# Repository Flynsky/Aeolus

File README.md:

# AEOLUS
### STM32 based Drone Ecosystem
<table align="center">
  <tr>
    <td align="center"><b>ESC Board</b></td>
    <td align="center"><b>Flight Controller</b></td>
  </tr>
  <tr>
    <td align="center">
      
    </td>
    <td align="center">
      
    </td>
  </tr>
  <tr>
    <td colspan="2" align="center"><b>Ground Station Controller</b></td>
  </tr>
  <tr>
    <td colspan="2" align="center">
      
    </td>
  </tr>
</table>

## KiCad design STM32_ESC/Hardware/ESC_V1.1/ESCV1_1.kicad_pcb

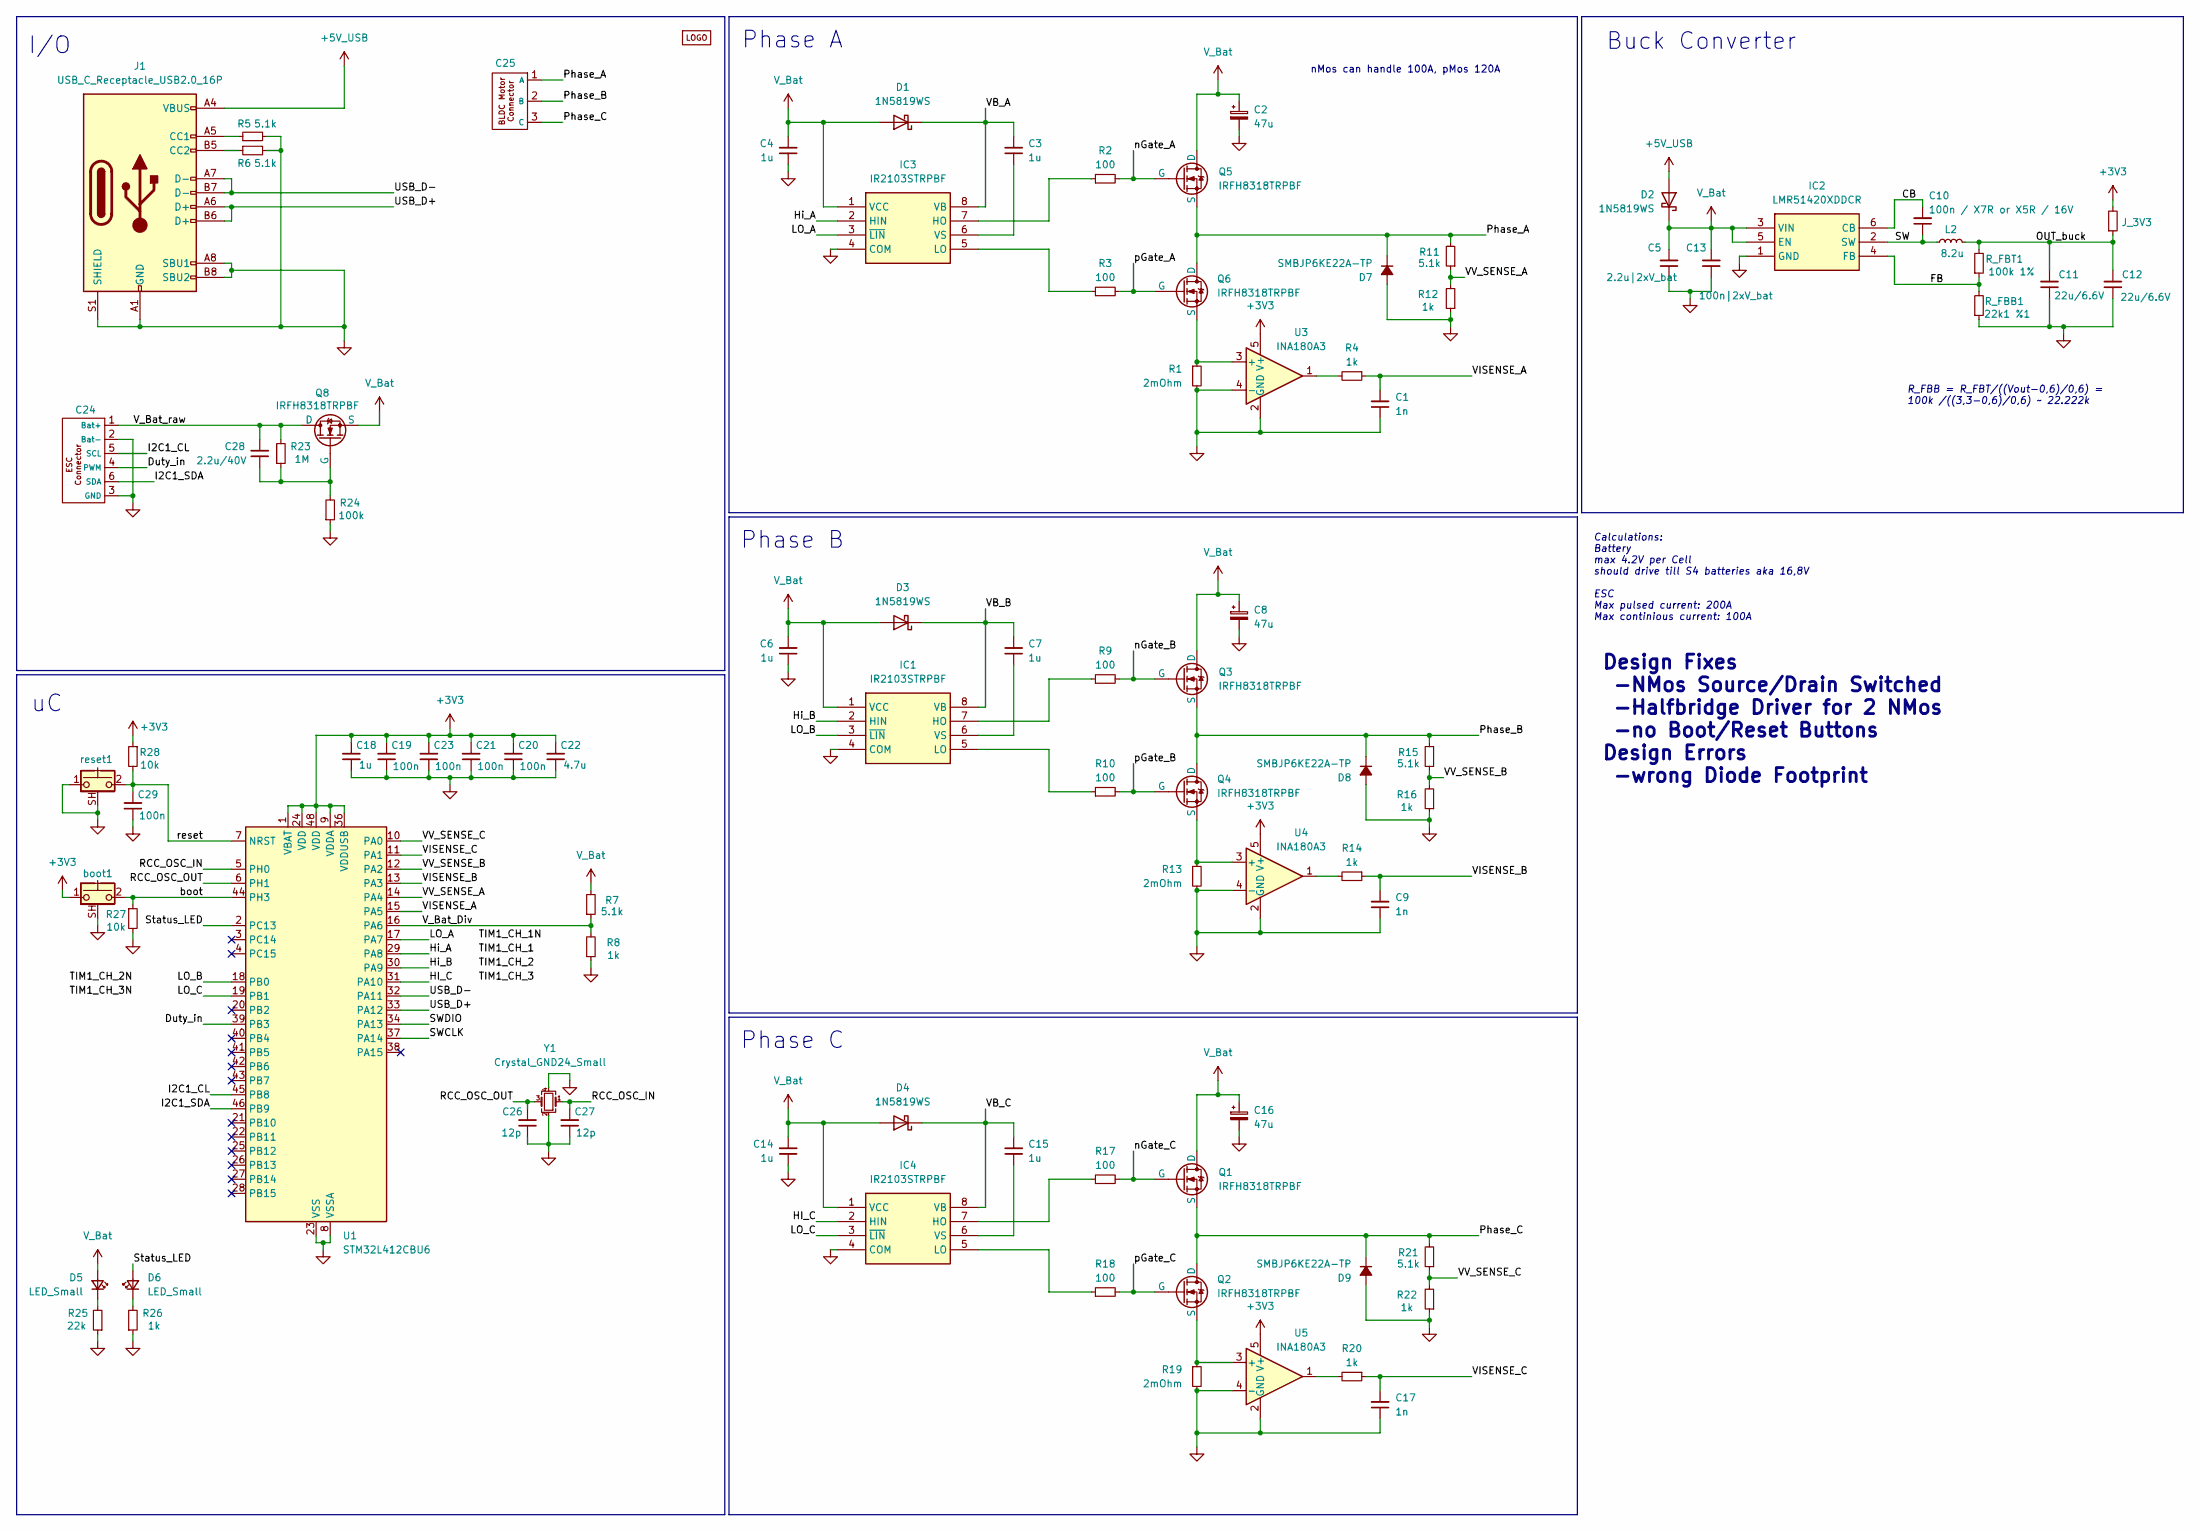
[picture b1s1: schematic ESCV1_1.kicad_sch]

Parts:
C1, C9, C17: 1n; C_0603_1608Metric
C2, C8, C16: 47u; Mouser Part Number 710-865080543009
C3, C4, C6, C7, C14, C15, C18: 1u; C_0603_1608Metric
C5: 2.2u|2xV_bat; C_0603_1608Metric
C10: 100n / X7R or X5R / 16V; C_0603_1608Metric
C11, C12: 22u/6.6V; C_0603_1608Metric
C13: 100n|2xV_bat; C_0402_1005Metric_Pad0.74x0.62mm_HandSolder
C19, C20, C21, C23, C29: 100n; C_0402_1005Metric
C22: 4.7u; C_0603_1608Metric
C24: Connector_ESC
C25: Connector_BLDC
C26, C27: 12p; C_0402_1005Metric
C28: 2.2u/40V; C_0603_1608Metric
D1, D2, D3, D4: 1N5819WS; D_SOD-323_HandSoldering
D5, D6: LED_Small; LED_0603_1608Metric
D7, D8, D9: SMBJP6KE22A-TP; D_SMB
IC1, IC3, IC4: IR2103STRPBF; Mouser Part Number 942-IR2103STRPBF
IC2: LMR51420XDDCR; Mouser Part Number 595-LMR51420XDDCR
J1: USB_C_Receptacle_USB2.0_16P; GSB1C41110SSHR
J_3V3: 0; R_0603_1608Metric
L2: 8.2u; Mouser Part Number 994-XAL5050-822MEC
Q1, Q2, Q3, Q4, Q5, Q6, Q8: IRFH8318TRPBF; BSC054N04NSGATMA1
R1, R13, R19: 2mOhm; R_2512_6332Metric; Mouser-Nr.: 603-PA2512FKM7W0R002
R2, R3, R9, R10, R17, R18: 100; R_0603_1608Metric
R4, R8, R12, R14, R16, R20, R22, R26: 1k; R_0603_1608Metric
R5, R6, R7, R11, R15, R21: 5.1k; R_0603_1608Metric
R23: 1M; R_0603_1608Metric
R24: 100k; R_0603_1608Metric
R25: 22k; R_0603_1608Metric
R27, R28: 10k; R_0603_1608Metric
R_FBB1: 22k1 %1; R_0603_1608Metric
R_FBT1: 100k 1%; R_0603_1608Metric
U1: STM32L412CBU6; QFN-48-1EP_7x7mm_P0.5mm_EP5.6x5.6mm
U3, U4, U5: INA180A3; SOT-23-5
U6: ESC_LOGO
Y1: Crystal_GND24_Small; ABM8W480000MHZ6D1XT3
boot1: CK_KMS2xxG; 435441019830
reset1: CK_KMS2xxG; 435441019830

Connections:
+3V3: C18.2, C19.2, C20.2, C21.2, C22.2, C23.2, J_3V3.2, R28.1, U1.1 (VBAT), U1.9 (VDDA), U1.24 (VDD), U1.36 (VDDUSB), U1.48 (VDD), U3.5 (V+), U4.5 (V+), U5.5 (V+), boot1.1
+5V_USB: D2.2 (A), J1.A4 (VBUS), J1.A9 (VBUS), J1.B4 (VBUS), J1.B9 (VBUS)
/CB: C10.2, IC2.6 (CB)
/Duty_in: C24.4 (PWM), U1.39 (PB3)
/FB: IC2.4 (FB), R_FBB1.2, R_FBT1.1
/HI_C: IC4.2 (HIN), U1.31 (PA10)
/Hi_A: IC3.2 (HIN), U1.29 (PA8)
/Hi_B: IC1.2 (HIN), U1.30 (PA9)
/I2C1_CL: C24.5 (SCL), U1.45 (PB8)
/I2C1_SDA: C24.6 (SDA), U1.46 (PB9)
/LO_A: IC3.3 (~LIN), U1.17 (PA7)
/LO_B: IC1.3 (~LIN), U1.18 (PB0)
/LO_C: IC4.3 (~LIN), U1.19 (PB1)
/OUT_buck: C11.2, C12.2, J_3V3.1, L2.2, R_FBT1.2
/Phase_A: C25.1 (A), D7.1 (K), Q5.S, Q6.D, R11.2
/Phase_B: C25.2 (B), D8.1 (K), Q3.S, Q4.D, R15.2
/Phase_C: C25.3 (C), D9.1 (K), Q1.S, Q2.D, R21.2
/RCC_OSC_IN: C27.2, U1.5 (PH0), Y1.1
/RCC_OSC_OUT: C26.2, U1.6 (PH1), Y1.3
/SW: C10.1, IC2.2 (SW), L2.1
/SWCLK: U1.37 (PA14)
/SWDIO: U1.34 (PA13)
/Status_LED: D6.2 (A), U1.2 (PC13)
/USB_D+: J1.A6 (D+), J1.B6 (D+), U1.33 (PA12)
/USB_D-: J1.A7 (D-), J1.B7 (D-), U1.32 (PA11)
/VB_A: C3.2, D1.1 (K), IC3.8 (VB)
/VB_B: C7.2, D3.1 (K), IC1.8 (VB)
/VB_C: C15.2, D4.1 (K), IC4.8 (VB)
/VISENSE_A: C1.2, R4.1, U1.15 (PA5)
/VISENSE_B: C9.2, R14.1, U1.13 (PA3)
/VISENSE_C: C17.2, R20.1, U1.11 (PA1)
/VV_SENSE_A: R11.1, R12.2, U1.14 (PA4)
/VV_SENSE_B: R15.1, R16.2, U1.12 (PA2)
/VV_SENSE_C: R21.1, R22.2, U1.10 (PA0)
/V_Bat_Div: R7.1, R8.2, U1.16 (PA6)
/V_Bat_raw: C24.1 (Bat+), C28.2, Q8.D, R23.2
/boot: R27.1, U1.44 (PH3), boot1.2
/nGate_A: Q5.G, R2.2
/nGate_B: Q3.G, R9.2
/nGate_C: Q1.G, R17.2
/pGate_A: Q6.G, R3.2
/pGate_B: Q4.G, R10.2
/pGate_C: Q2.G, R18.2
/reset: C29.2, R28.2, U1.7 (NRST), reset1.2
GND: C1.1, C2.2, C4.1, C5.1, C6.1, C8.2, C9.1, C11.1, C12.1, C13.1, C14.1, C16.2, C17.1, C18.1, C19.1, C20.1, C21.1, C22.1, C23.1, C24.2 (Bat-), C24.3 (GND), C26.1, C27.1, C29.1, D7.2 (A), D8.2 (A), D9.2 (A), IC1.4 (COM), IC2.1 (GND), IC3.4 (COM), IC4.4 (COM), J1.A1 (GND), J1.A8 (SBU1), J1.A12 (GND), J1.B1 (GND), J1.B8 (SBU2), J1.B12 (GND), J1.S1 (SHIELD), R1.2, R5.2, R6.2, R8.1, R12.1, R13.2, R16.1, R19.2, R22.1, R24.1, R25.1, R26.1, R27.2, R_FBB1.1, U1.8 (VSSA), U1.23 (VSS), U1.35 (VSS), U1.47 (VSS), U1.49 (VSS), U3.2 (GND), U3.4 (-), U4.2 (GND), U4.4 (-), U5.2 (GND), U5.4 (-), Y1.2, Y1.4, boot1.SH (B), reset1.1, reset1.SH (B)
unnamed: C28.1, Q8.G, R23.1, R24.2
unnamed: D5.1 (K), R25.2
unnamed: D6.1 (K), R26.2
unnamed: IC1.7 (HO), R9.1
unnamed: IC1.5 (LO), R10.1
unnamed: C7.1, IC1.6 (VS)
unnamed: IC3.7 (HO), R2.1
unnamed: IC3.5 (LO), R3.1
unnamed: C3.1, IC3.6 (VS)
unnamed: IC4.7 (HO), R17.1
unnamed: IC4.5 (LO), R18.1
unnamed: C15.1, IC4.6 (VS)
unnamed: J1.A5 (CC1), R5.1
unnamed: J1.B5 (CC2), R6.1
unnamed: R4.2, U3.1
unnamed: R14.2, U4.1
unnamed: R20.2, U5.1
unnamed: Q6.S, R1.1, U3.3 (+)
unnamed: Q4.S, R13.1, U4.3 (+)
unnamed: Q2.S, R19.1, U5.3 (+)
V_Bat: C2.1, C4.2, C5.2, C6.2, C8.1, C13.2, C14.2, C16.1, D1.2 (A), D2.1 (K), D3.2 (A), D4.2 (A), D5.2 (A), IC1.1 (VCC), IC2.3 (VIN), IC2.5 (EN), IC3.1 (VCC), IC4.1 (VCC), Q1.D, Q3.D, Q5.D, Q8.S, R7.2

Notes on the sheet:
Phase A
nMos can handle 100A, pMos 120A
Design Fixes -NMos Source/Drain Switched -Halfbridge Driver for 2 NMos -no Boot/Reset Buttons Design Errors -wrong Diode Footprint
I/O
Buck Converter
Phase B
Phase C
Calculations: Battery max 4.2V per Cell should drive till S4 batteries aka 16,8V ESC Max pulsed current: 200A Max continious current: 100A
R_FBB = R_FBT/((Vout-0,6)/0,6) = 100k /((3,3-0,6)/0,6) ~ 22.222k

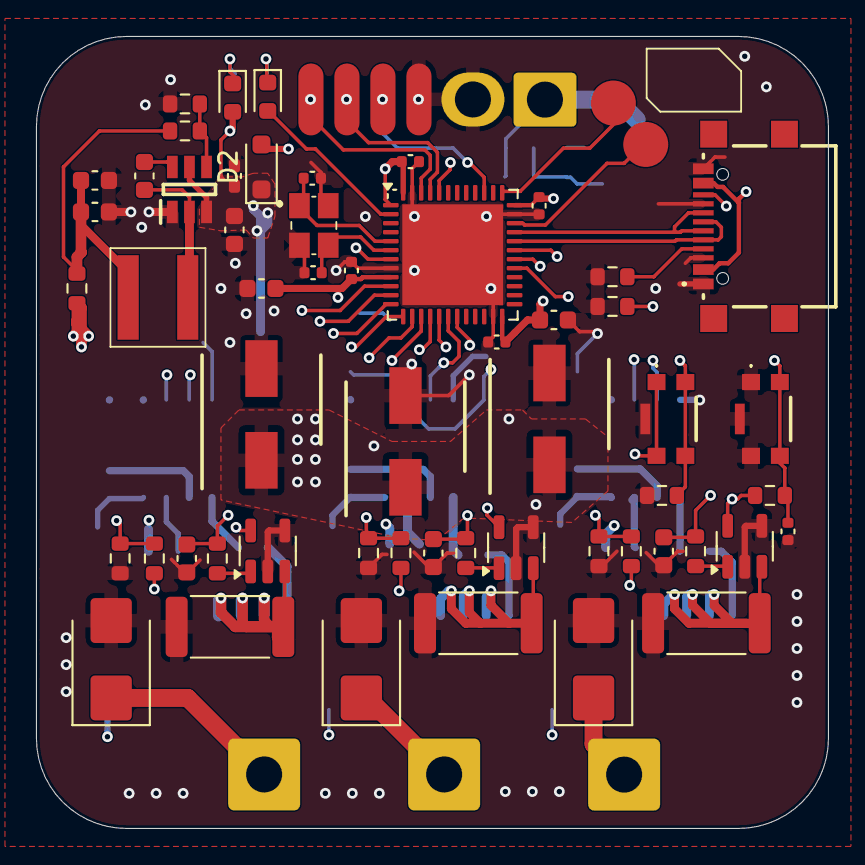
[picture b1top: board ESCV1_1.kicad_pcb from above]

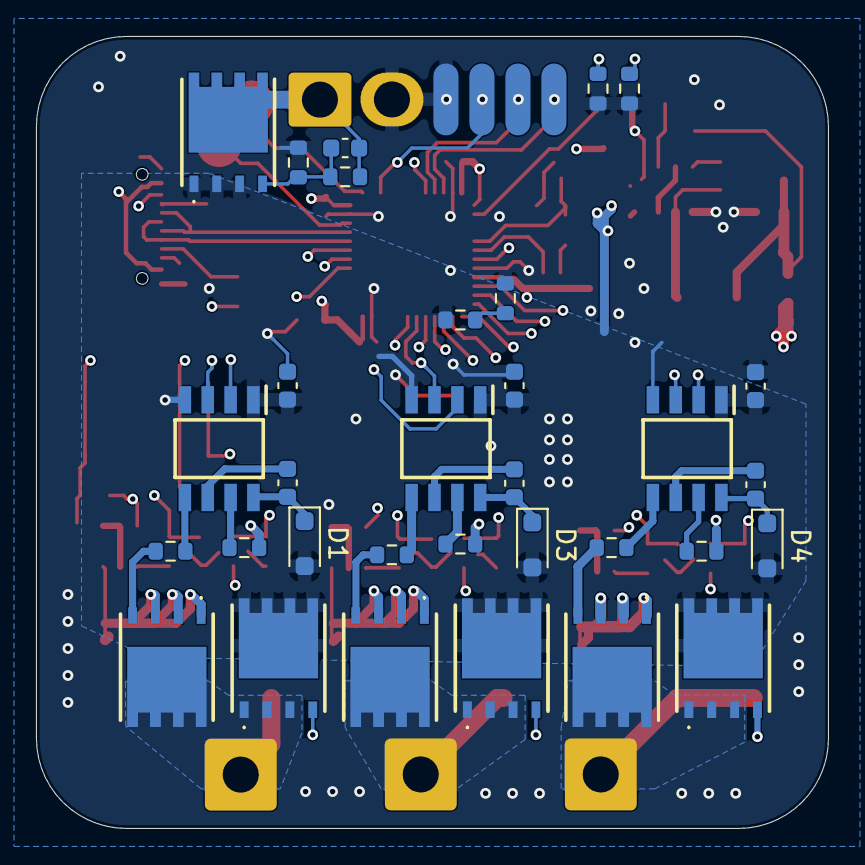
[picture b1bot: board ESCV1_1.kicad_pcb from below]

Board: 4 copper layers, 44.0 x 44.0 mm, 90 parts (32 on the bottom side), 64 nets.

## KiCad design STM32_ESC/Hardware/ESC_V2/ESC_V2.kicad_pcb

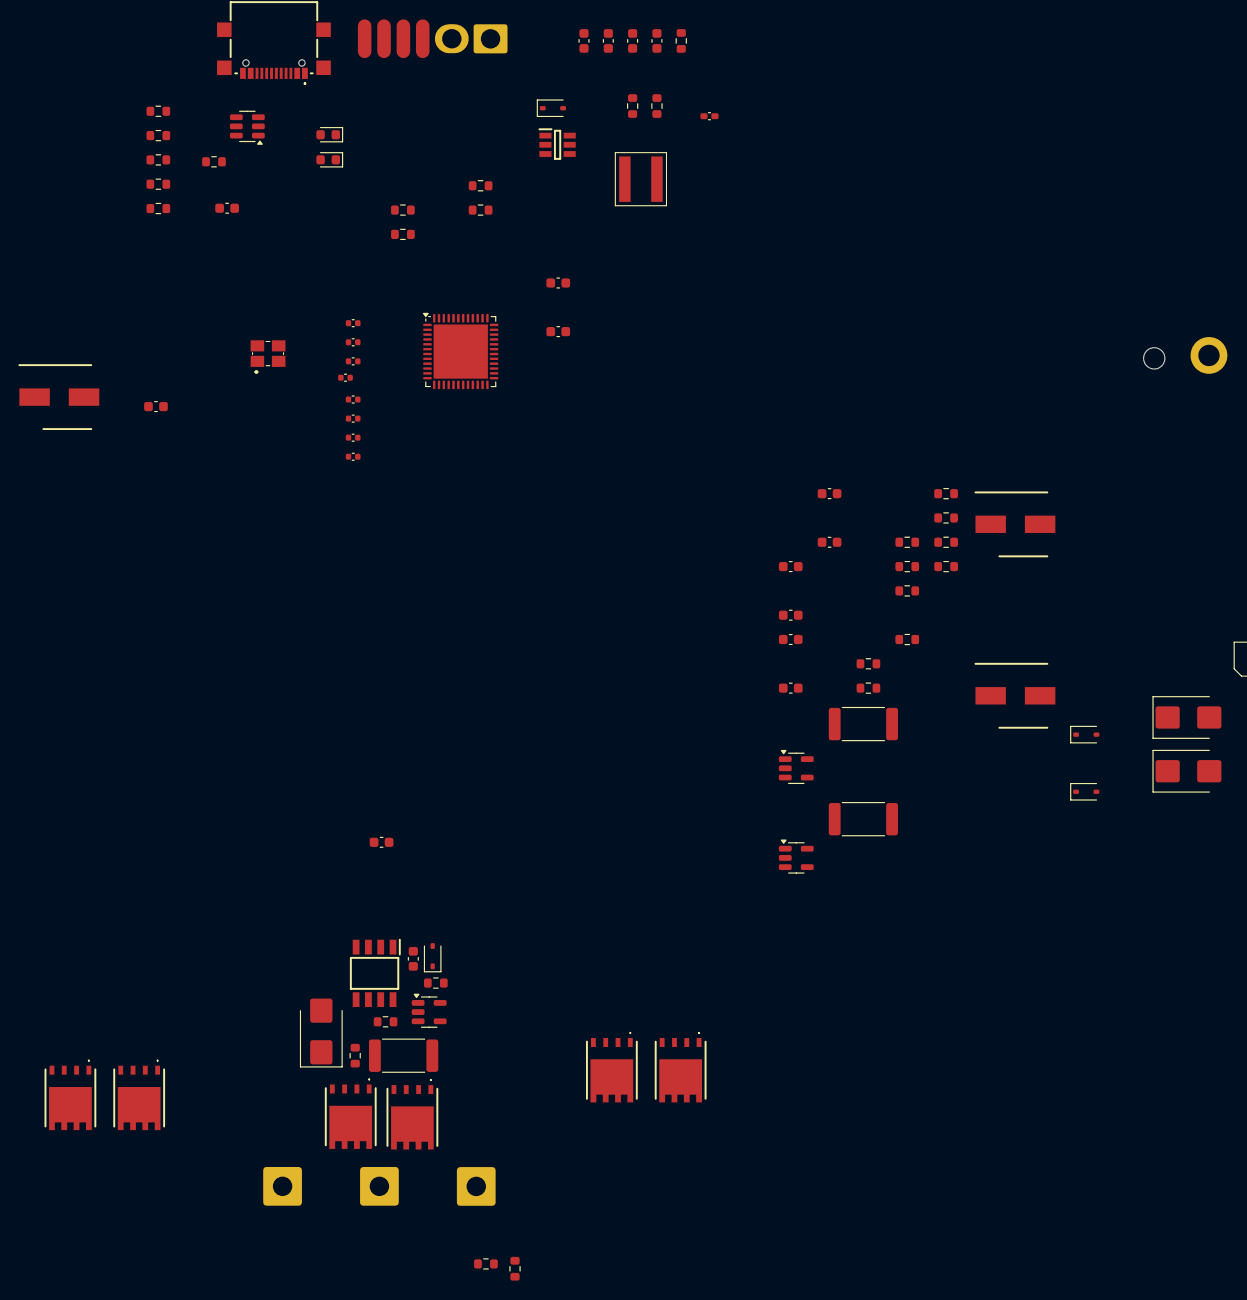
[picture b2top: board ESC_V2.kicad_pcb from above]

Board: 2 copper layers, 89 parts (0 on the bottom side), 55 nets, no tracks yet.

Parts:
C1: Connector_ESC
C2: 4.7u; C_0603_1608Metric
C3, C4, C6, C7, C29, C30: 100n; C_0402_1005Metric
C5: 2.2u/40V; C_0603_1608Metric
C8, C12, C13, C14, C15, C16, C17: 1u; C_0603_1608Metric
C9: Connector_BLDC
C10, C11: 12p; C_0402_1005Metric
C18, C19, C20: 47u; CAPAE660X550N
C21, C22, C23: 1n; C_0603_1608Metric
C24: 2.2u / 2xV_bat; C_0603_1608Metric
C25: 100n /2x V_bat; C_0402_1005Metric_Pad0.74x0.62mm_HandSolder
C26: 100n / X7R or X5R / 16V; C_0603_1608Metric
C27, C28: 22u/6.6V; C_0603_1608Metric
D1, D2: LED_Small; LED_0603_1608Metric
D3, D4, D5, D9: 1N5819WS; D_SOD-323
D6, D7, D8: SMBJP6KE22A-TP; D_SMB
H1: MountingHole; MountingHole_2.2mm_M2_DIN965_Pad
H2: MountingHole; MountingHole_2.2mm_M2
IC2: IR2103STRPBF; SOIC127P600X175-8N
IC4: LMR51420XDDCR; SOT95P280X110-6N
J1: USB_C_Receptacle_USB2.0_16P; GSB1C41110SSHR
J_3V1: 0; R_0603_1608Metric
L1: 8.2u; XAL5050822MEC
Q1, Q2, Q3, Q4, Q5, Q6: N-MOS IRFH8318TRPBF; BSC054N04NSGATMA1
R1, R2, R7, R21, R23, R25: 5.1k; R_0603_1608Metric
R3: 1M; R_0603_1608Metric
R4, R27, R28: 100k; R_0603_1608Metric
R5: 22k; R_0603_1608Metric
R6, R8, R18, R19, R20, R22, R24, R26: 1k; R_0603_1608Metric
R9, R10, R11, R12, R13, R14: 100; R_0603_1608Metric
R15, R16, R17: 2mOhm; R_2512_6332Metric
R_FBB1: 22k1 %1; R_0603_1608Metric
R_FBT1: 100k 1%; R_0603_1608Metric
U1: STM32L412CBU6; QFN-48-1EP_7x7mm_P0.5mm_EP5.6x5.6mm
U2: USBLC6-2SC6; SOT-23-6
U3: ESC_LOGO
U4, U5, U6: INA180A3; SOT-23-5
Y1: Crystal_GND24_Small; ABM8W480000MHZ6D1XT3

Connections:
+3V3: C2.2, C3.2, C4.2, C6.2, C7.2, C8.2, D2.2 (A), J_3V1.2, U1.1 (VBAT), U1.9 (VDDA), U1.24 (VDD), U1.36 (VDDUSB), U1.48 (VDD), U4.5 (V+), U5.5 (V+), U6.5 (V+)
+5V_USB: D9.2 (A), J1.A4 (VBUS), J1.A9 (VBUS), U2.5 (VBUS)
/CB: C26.2, IC4.6 (CB)
/Duty_in: C1.4 (PWM), U1.39 (PB3)
/FB: IC4.4 (FB), R_FBB1.2, R_FBT1.1
/Hi_B: IC2.2 (HIN), U1.30 (PA9)
/I2C1_CL: C1.5 (SCL), U1.45 (PB8)
/I2C1_SDA: C1.6 (SDA), U1.46 (PB9)
/LO_B: IC2.3 (~LIN), U1.18 (PB0)
/OUT_buck: C27.2, C28.2, J_3V1.1, L1.2, R_FBT1.2
/Phase_A: C9.1 (A), D8.1 (K), Q1.3 (D), Q2.1 (S), R25.2
/Phase_B: C9.2 (B), D6.1 (K), Q3.1 (S), Q4.3 (D), R21.2
/Phase_C: C9.3 (C), D7.1 (K), Q5.1 (S), Q6.3 (D), R23.2
/RCC_OSC_IN: C11.2, U1.5 (PH0), Y1.1
/RCC_OSC_OUT: C10.2, U1.6 (PH1), Y1.3
/SW: C26.1, IC4.2 (SW), L1.1
/USB_D+: U1.33 (PA12), U2.4 (I/O2)
/USB_D-: U1.32 (PA11), U2.6 (I/O1)
/VB_A: C15.2, D3.1 (K)
/VB_B: C16.2, D4.1 (K), IC2.8 (VB)
/VB_C: C17.2, D5.1 (K)
/VISENSE_A: C21.2, R18.1, U1.15 (PA5)
/VISENSE_B: C22.2, R19.1, U1.13 (PA3)
/VISENSE_C: C23.2, R20.1, U1.11 (PA1)
/VV_SENSE_A: R25.1, R26.2, U1.14 (PA4)
/VV_SENSE_B: R21.1, R22.2, U1.12 (PA2)
/VV_SENSE_C: R23.1, R24.2, U1.10 (PA0)
/V_Bat_Div: R7.1, R8.2, U1.16 (PA6)
/V_Bat_raw: C1.1 (Bat+), C5.2, R3.2
/nGate_A: Q2.2 (G), R9.2
/nGate_B: Q3.2 (G), R11.2
/nGate_C: Q5.2 (G), R13.2
/pGate_A: Q1.2 (G), R10.2
/pGate_B: Q4.2 (G), R12.2
/pGate_C: Q6.2 (G), R14.2
GND: C1.2 (Bat-), C1.3 (GND), C2.1, C3.1, C4.1, C6.1, C7.1, C8.1, C10.1, C11.1, C12.1, C13.1, C14.1, C18.2, C19.2, C20.2, C21.1, C22.1, C23.1, C24.1, C25.1, C27.1, C28.1, C29.1, C30.1, D6.2 (A), D7.2 (A), D8.2 (A), IC2.4 (COM), IC4.1 (GND), J1.A1 (GND), J1.A8 (SBU1), J1.A12 (GND), J1.B8 (SBU2), R1.2, R2.2, R4.1, R5.1, R6.1, R8.1, R15.2, R16.2, R17.2, R22.1, R24.1, R26.1, R27.1, R28.1, R_FBB1.1, U1.8 (VSSA), U1.23 (VSS), U1.35 (VSS), U1.47 (VSS), U1.49 (VSS), U2.2 (GND), U4.2 (GND), U4.4 (-), U5.2 (GND), U5.4 (-), U6.2 (GND), U6.4 (-), Y1.2, Y1.4
unnamed: C5.1, R3.1, R4.2
unnamed: D1.1 (K), R5.2
unnamed: D2.1 (K), R6.2
unnamed: IC2.7 (HO), R11.1
unnamed: IC2.5 (LO), R12.1
unnamed: C16.1, IC2.6 (VS)
unnamed: J1.A5 (CC1), R1.1
unnamed: J1.B5 (CC2), R2.1
unnamed: J1.A6 (D+), J1.B6 (D+), U2.3 (I/O2)
unnamed: J1.A7 (D-), J1.B7 (D-), U2.1 (I/O1)
unnamed: Q1.1 (S), R15.1, U4.3 (+)
unnamed: Q4.1 (S), R16.1, U5.3 (+)
unnamed: Q6.1 (S), R17.1, U6.3 (+)
unnamed: R18.2, U4.1
unnamed: R19.2, U5.1
unnamed: R20.2, U6.1
unnamed: C29.2, R27.2, U1.44 (PH3)
unnamed: C30.2, R28.2, U1.7 (NRST)
V_Bat: C12.2, C13.2, C14.2, C18.1, C19.1, C20.1, C24.2, C25.2, D1.2 (A), D3.2 (A), D4.2 (A), D5.2 (A), D9.1 (K), IC2.1 (VCC), IC4.3 (VIN), IC4.5 (EN), Q2.3 (D), Q3.3 (D), Q5.3 (D), R7.2

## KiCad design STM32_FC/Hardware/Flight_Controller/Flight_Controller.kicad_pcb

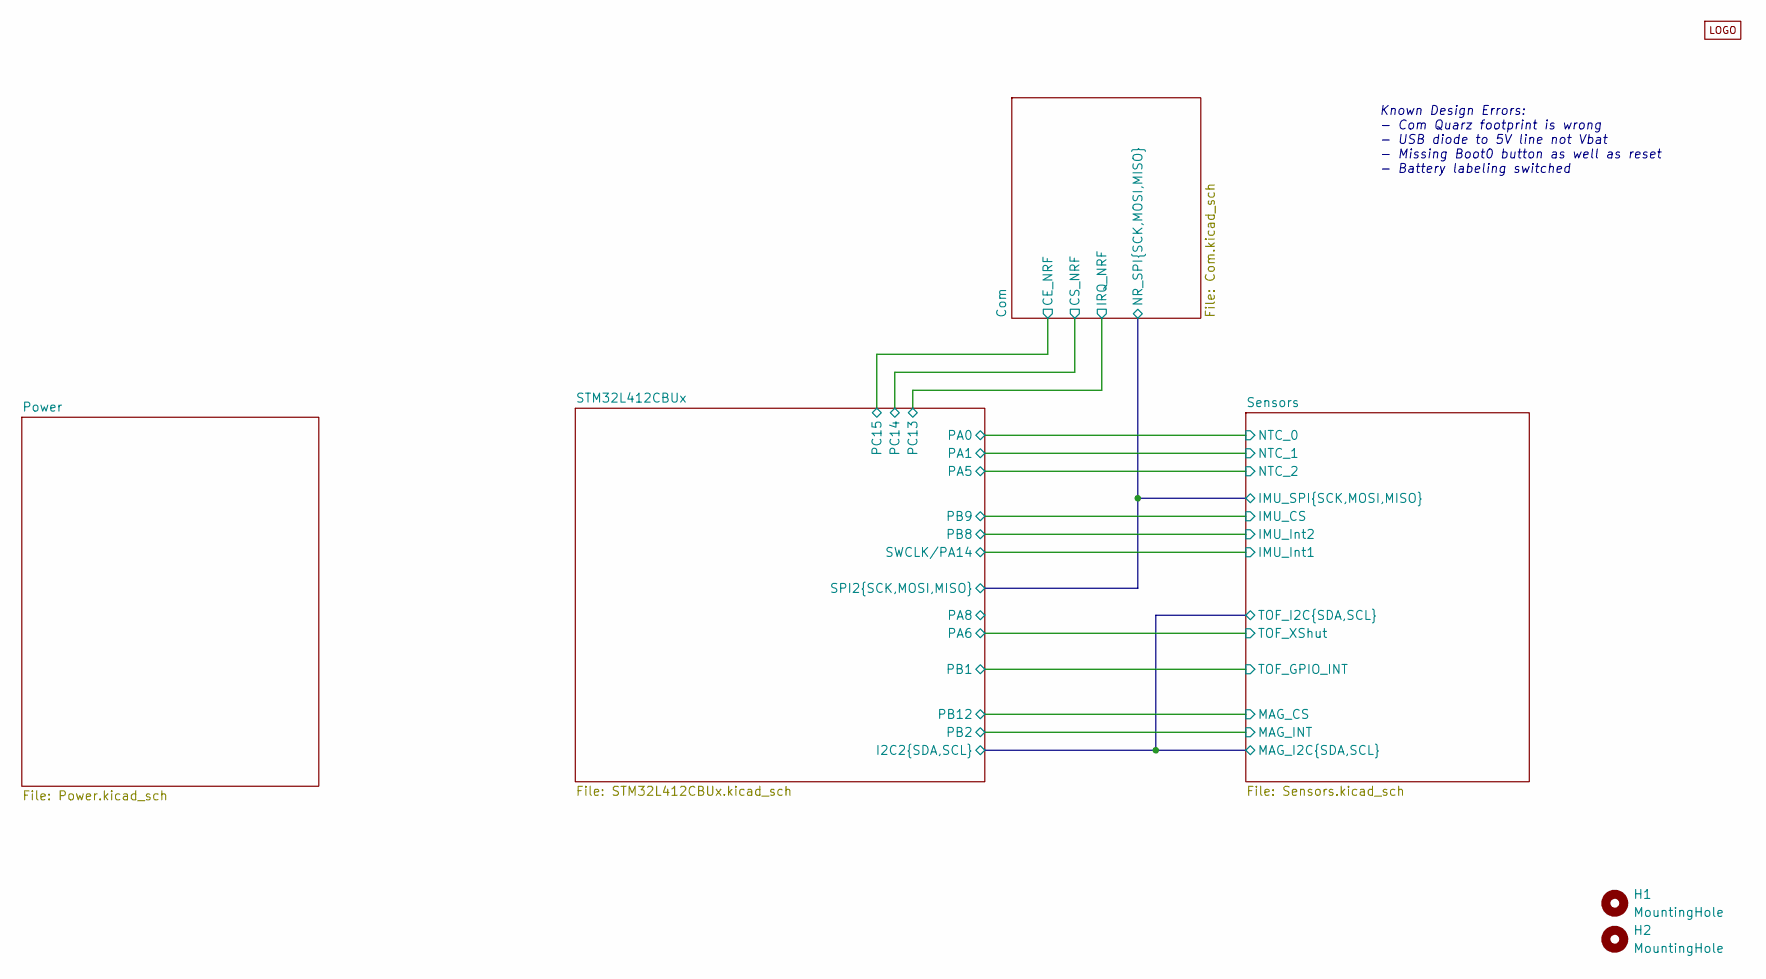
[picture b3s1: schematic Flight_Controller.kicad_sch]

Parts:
H1: MountingHole; MountingHole_2.2mm_M2_DIN965_Pad
H2: MountingHole; MountingHole_2.2mm_M2
U6: ESC_LOGO

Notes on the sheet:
Known Design Errors: - Com Quarz footprint is wrong - USB diode to 5V line not Vbat - Missing Boot0 button as well as reset - Battery labeling switched

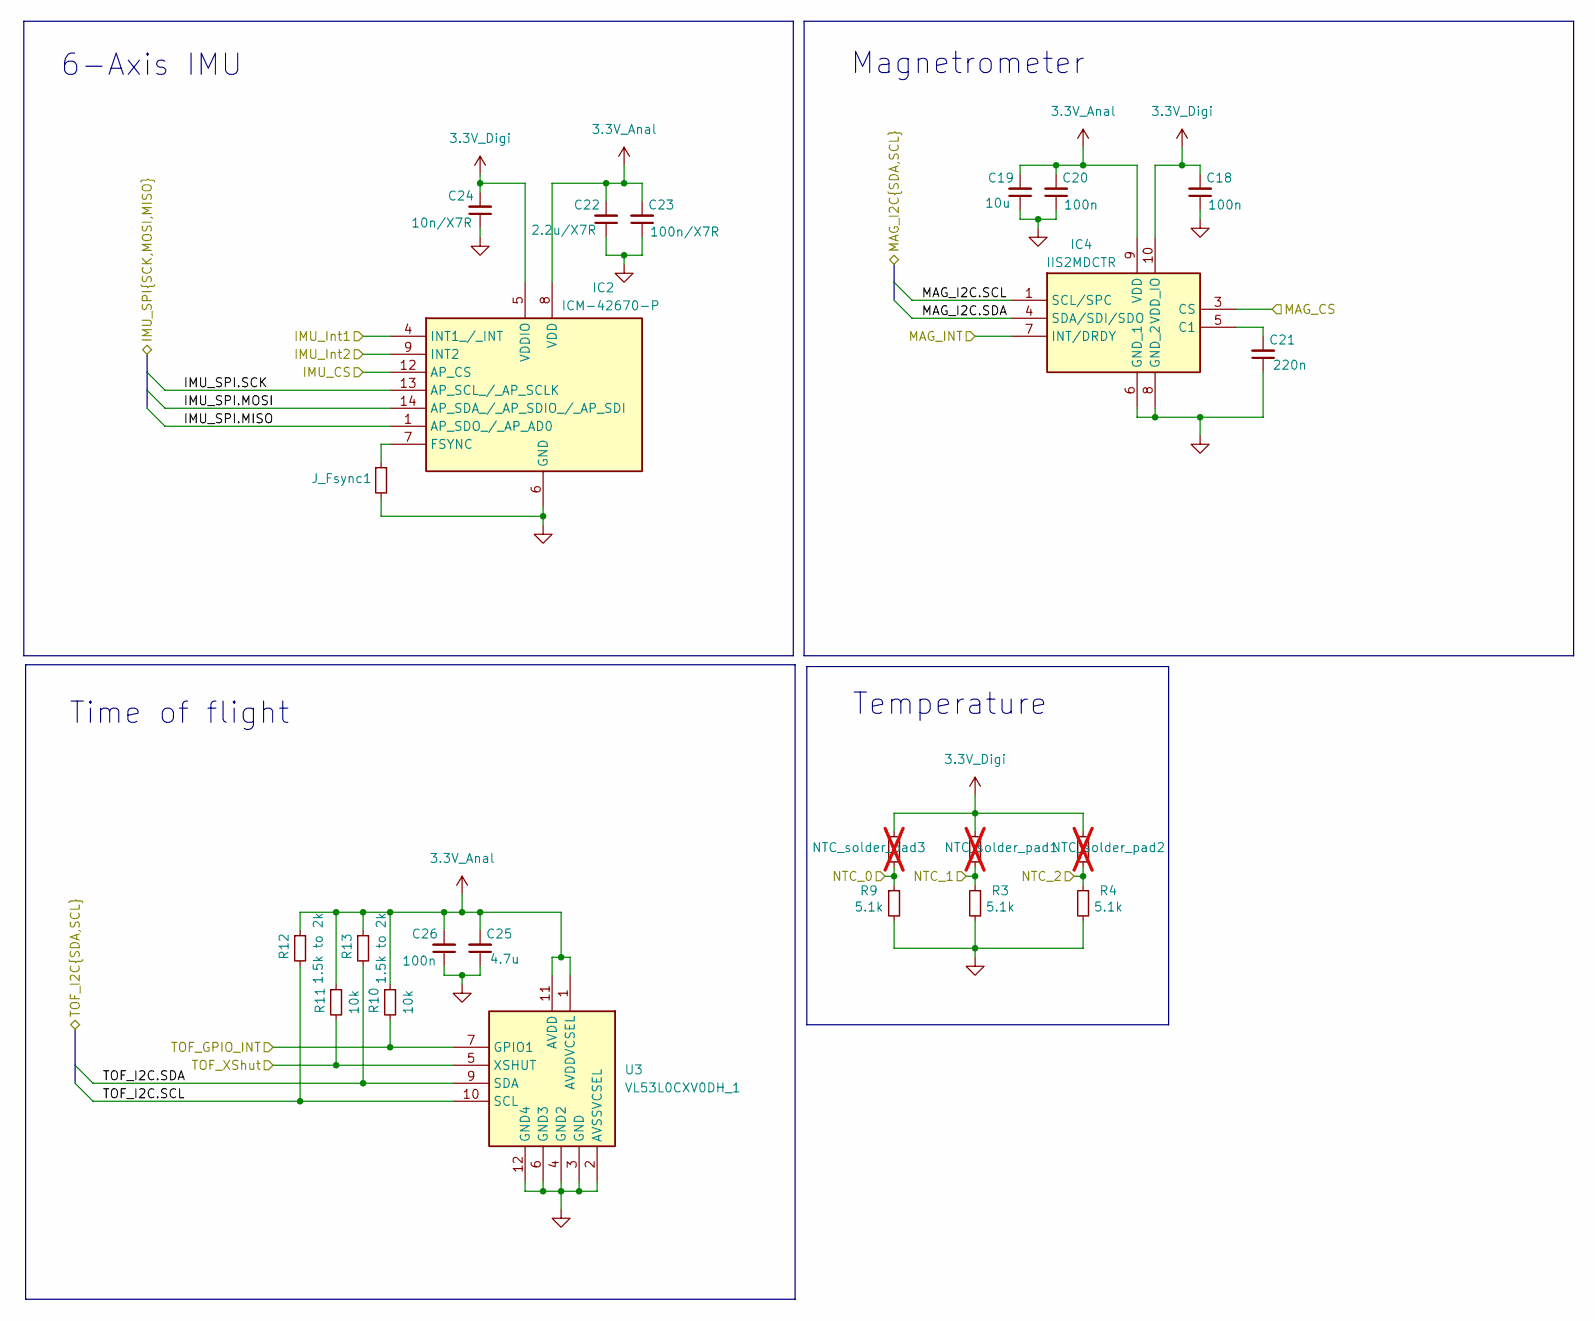
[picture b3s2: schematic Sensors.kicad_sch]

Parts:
C18, C20, C26: 100n; C_0402_1005Metric
C19: 10u; C_0603_1608Metric
C21: 220n; C_0603_1608Metric
C22: 2.2u/X7R; C_0603_1608Metric
C23: 100n/X7R; C_0402_1005Metric
C24: 10n/X7R; C_0402_1005Metric
C25: 4.7u; C_0603_1608Metric
IC2: ICM-42670-P; ICM42670P; Mouser Part Number 410-ICM-42670-P
IC4: IIS2MDCTR; Mouser Part Number 511-IIS2MDCTR
J_Fsync1: 0; R_0603_1608Metric
NTC_solder_pad1, NTC_solder_pad2, NTC_solder_pad3: 0; R_0805_2012Metric_Pad1.20x1.40mm_HandSolder; not fitted
R3, R4, R9: 5.1k; R_0603_1608Metric
R10, R11: 10k; R_0603_1608Metric
R12, R13: 1.5k to 2k; R_0603_1608Metric
U3: VL53L0CXV0DH_1; LGA12_1; Mouser Part Number 511-VL53L0CXV0DH/1

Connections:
3.3V_Anal: C19.2, C20.2, C22.2, C23.2, C25.2, C26.2, IC2.8 (VDD), IC4.9 (VDD), R10.1, R11.1, R12.1, R13.1, U3.1 (AVDDVCSEL), U3.11 (AVDD); also elsewhere on the board
3.3V_Digi: C18.2, C24.2, IC2.5 (VDDIO), IC4.10 (VDD_IO), NTC_solder_pad1.1, NTC_solder_pad2.1, NTC_solder_pad3.1; also elsewhere on the board
/Com/NR_SPI.MISO: IC2.1 (AP_SDO_/_AP_AD0); also elsewhere on the board
/Com/NR_SPI.MOSI: IC2.14 (AP_SDA_/_AP_SDIO_/_AP_SDI); also elsewhere on the board
/Com/NR_SPI.SCK: IC2.13 (AP_SCL_/_AP_SCLK); also elsewhere on the board
/STM32L412CBUx/PA0: NTC_solder_pad3.2, R9.1; also elsewhere on the board
/STM32L412CBUx/PA1: NTC_solder_pad1.2, R3.1; also elsewhere on the board
/STM32L412CBUx/PA5: NTC_solder_pad2.2, R4.1; also elsewhere on the board
/STM32L412CBUx/PA6: R11.2, U3.5 (XSHUT); also elsewhere on the board
/STM32L412CBUx/PB1: R10.2, U3.7 (GPIO1); also elsewhere on the board
/STM32L412CBUx/PB2: IC4.7 (INT/DRDY); also elsewhere on the board
/STM32L412CBUx/PB8: IC2.9 (INT2); also elsewhere on the board
/STM32L412CBUx/PB9: IC2.12 (AP_CS); also elsewhere on the board
/STM32L412CBUx/PB12: IC4.3 (CS); also elsewhere on the board
/STM32L412CBUx/SWCLK/PA14: IC2.4 (INT1_/_INT); also elsewhere on the board
GND: C18.1, C19.1, C20.1, C21.1, C22.1, C23.1, C24.1, C25.1, C26.1, IC2.6 (GND), IC4.6 (GND_1), IC4.8 (GND_2), J_Fsync1.2, R3.2, R4.2, R9.2, U3.2 (AVSSVCSEL), U3.3 (GND), U3.4 (GND2), U3.6 (GND3), U3.12 (GND4); also elsewhere on the board
unnamed: IC2.7 (FSYNC), J_Fsync1.1
unnamed: C21.2, IC4.5 (C1)

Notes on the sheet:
Temperature
6-Axis IMU
Magnetrometer
Time of flight

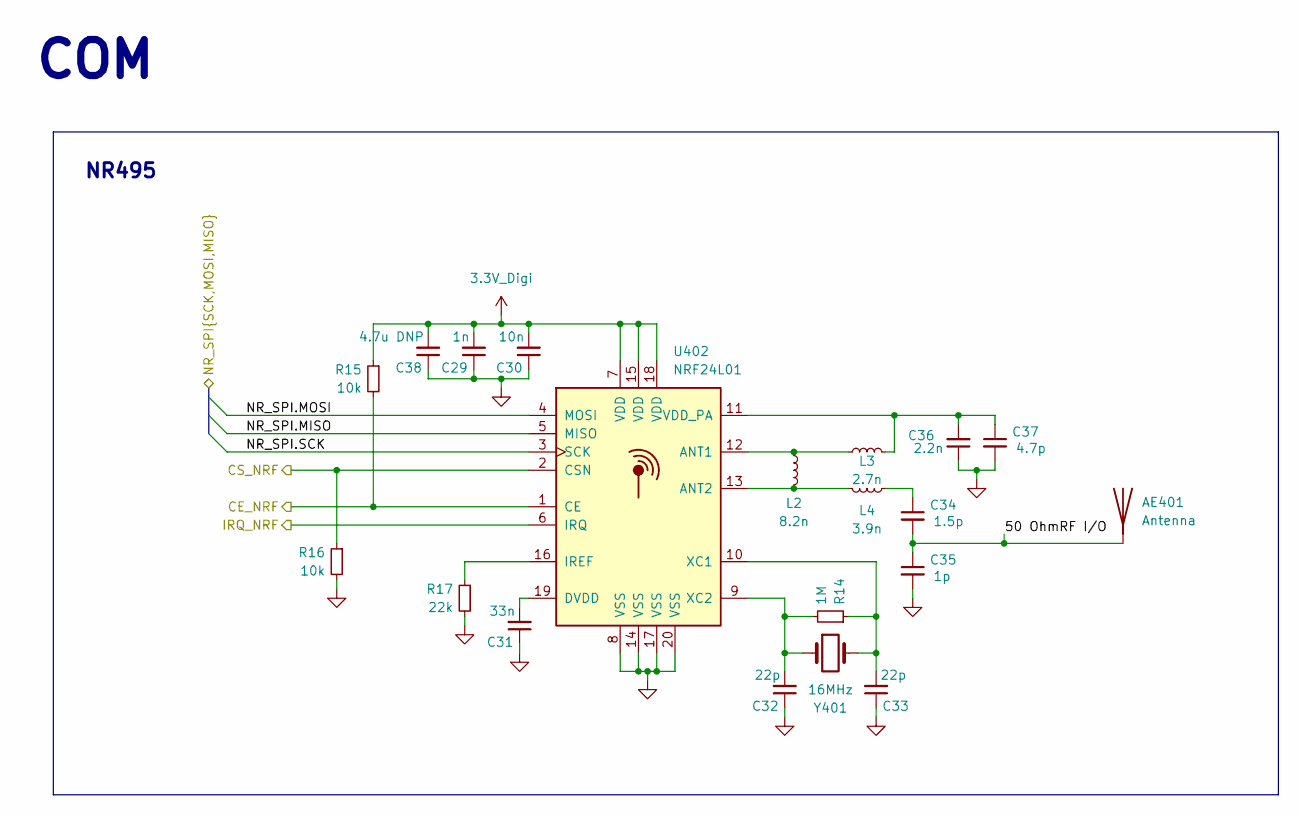
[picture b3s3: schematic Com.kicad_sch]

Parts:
AE401: Antenna
C29: 1n; C_0402_1005Metric
C30: 10n; C_0402_1005Metric
C31: 33n; C_0402_1005Metric
C32, C33: 22p; C_0402_1005Metric
C34: 1.5p; C_0402_1005Metric
C35: 1p; C_0402_1005Metric
C36: 2.2n; C_0402_1005Metric
C37: 4.7p; C_0402_1005Metric
C38: 4.7u DNP; C_0603_1608Metric
L2: 8.2n; R_0402_1005Metric
L3: 2.7n; R_0402_1005Metric
L4: 3.9n; R_0402_1005Metric
R14: 1M; R_0603_1608Metric
R15, R16: 10k; R_0603_1608Metric
R17: 22k; R_0603_1608Metric
U402: NRF24L01; QFN-20-1EP_4x4mm_P0.5mm_EP2.5x2.5mm
Y401: 16MHz; Crystal_SMD_2012-2Pin_2.0x1.2mm

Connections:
3.3V_Digi: C29.2, C30.2, C38.2, R15.1; also elsewhere on the board
/Com/50 OhmRF I/O: AE401.1, C34.2, C35.1
/Com/CE_NRF: R15.2; also elsewhere on the board
/Com/CS_NRF: R16.1; also elsewhere on the board
GND: C29.1, C30.1, C31.1, C32.1, C33.1, C35.2, C36.1, C37.2, C38.1, R16.2, R17.2; also elsewhere on the board
unnamed: C34.1, L4.2
unnamed 56: L2.1, L3.2; also elsewhere on the board
unnamed 57: L2.2, L4.1; also elsewhere on the board
unnamed 58: C31.2; also elsewhere on the board
unnamed 59: R17.1; also elsewhere on the board
unnamed 60: C36.2, C37.1, L3.1; also elsewhere on the board
unnamed 61: C33.2, R14.1; also elsewhere on the board
unnamed 62: C32.2, R14.2; also elsewhere on the board

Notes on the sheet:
NR495
COM

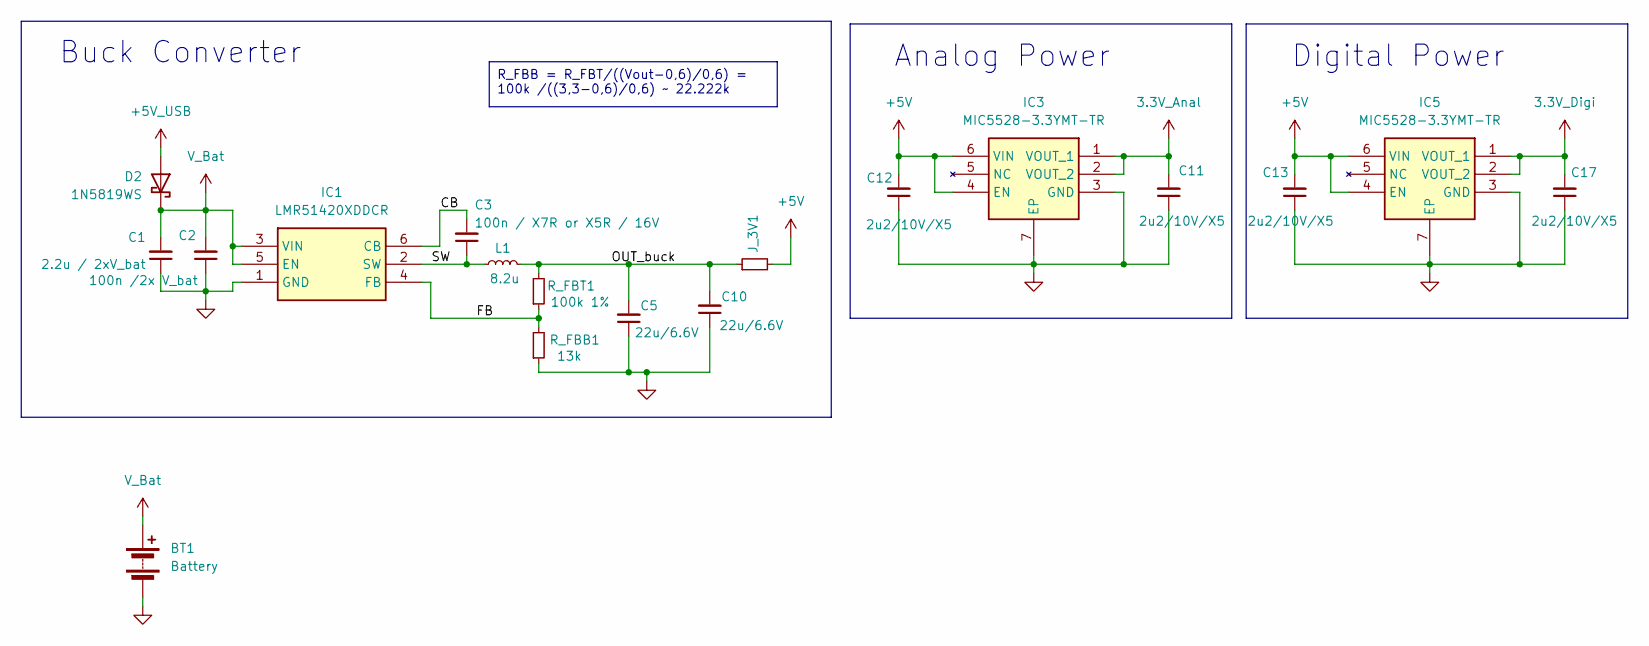
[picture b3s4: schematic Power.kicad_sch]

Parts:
BT1: Battery; AMASS_XT30U-F_1x02_P5.0mm_Vertical
C1: 2.2u / 2xV_bat; C_0603_1608Metric
C2: 100n /2x V_bat; C_0402_1005Metric_Pad0.74x0.62mm_HandSolder
C3: 100n / X7R or X5R / 16V; C_0603_1608Metric
C5, C10: 22u/6.6V; C_0603_1608Metric
C11, C12, C13, C17: 2u2/10V/X5; C_0603_1608Metric
D2: 1N5819WS; D_SOD-323
IC1: LMR51420XDDCR; SOT95P280X110-6N; Mouser Part Number 595-LMR51420XDDCR
IC3, IC5: MIC5528-3.3YMT-TR; SON40P120X120X60-7N-D; Mouser Part Number 998-MIC5528-3.3YMTTR
J_3V1: 0; R_0603_1608Metric
L1: 8.2u; XAL5050822MEC; Mouser Part Number 994-XAL5050-822MEC
R_FBB1: 13k; R_0603_1608Metric
R_FBT1: 100k 1%; R_0603_1608Metric

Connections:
3.3V_Anal: C11.2, IC3.1 (VOUT_1), IC3.2 (VOUT_2); also elsewhere on the board
3.3V_Digi: C17.2, IC5.1 (VOUT_1), IC5.2 (VOUT_2); also elsewhere on the board
+5V: C12.2, C13.2, IC3.4 (EN), IC3.6 (VIN), IC5.4 (EN), IC5.6 (VIN), J_3V1.2
+5V_USB: D2.2 (A); also elsewhere on the board
/Power/CB: C3.2, IC1.6 (CB)
/Power/FB: IC1.4 (FB), R_FBB1.2, R_FBT1.1
/Power/OUT_buck: C5.2, C10.2, J_3V1.1, L1.2, R_FBT1.2
/Power/SW: C3.1, IC1.2 (SW), L1.1
GND: BT1.2 (-), C1.1, C2.1, C5.1, C10.1, C11.1, C12.1, C13.1, C17.1, IC1.1 (GND), IC3.3 (GND), IC3.7 (EP), IC5.3 (GND), IC5.7 (EP), R_FBB1.1; also elsewhere on the board
V_Bat: BT1.1 (+), C1.2, C2.2, D2.1 (K), IC1.3 (VIN), IC1.5 (EN); also elsewhere on the board

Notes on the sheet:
R_FBB = R_FBT/((Vout-0,6)/0,6) = 100k /((3,3-0,6)/0,6) ~ 22.222k
Buck Converter
Analog Power
Digital Power
